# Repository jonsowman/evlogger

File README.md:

Electric Vehicle Datalogger
===========================

This project uses an MSP430 (specifically, the MSP430F5529) to log data from
various channels to be used on an electric vehicle. This project is designed
for use on the MSP-EXP430F5529LP experimentation board which is available from
Texas Instruments.  

Documentation at http://jonsowman.github.com/evlogger.  

Released into the public domain by Jon Sowman, 2014.  

[Get in touch](mailto:j.sowman@soton.ac.uk)

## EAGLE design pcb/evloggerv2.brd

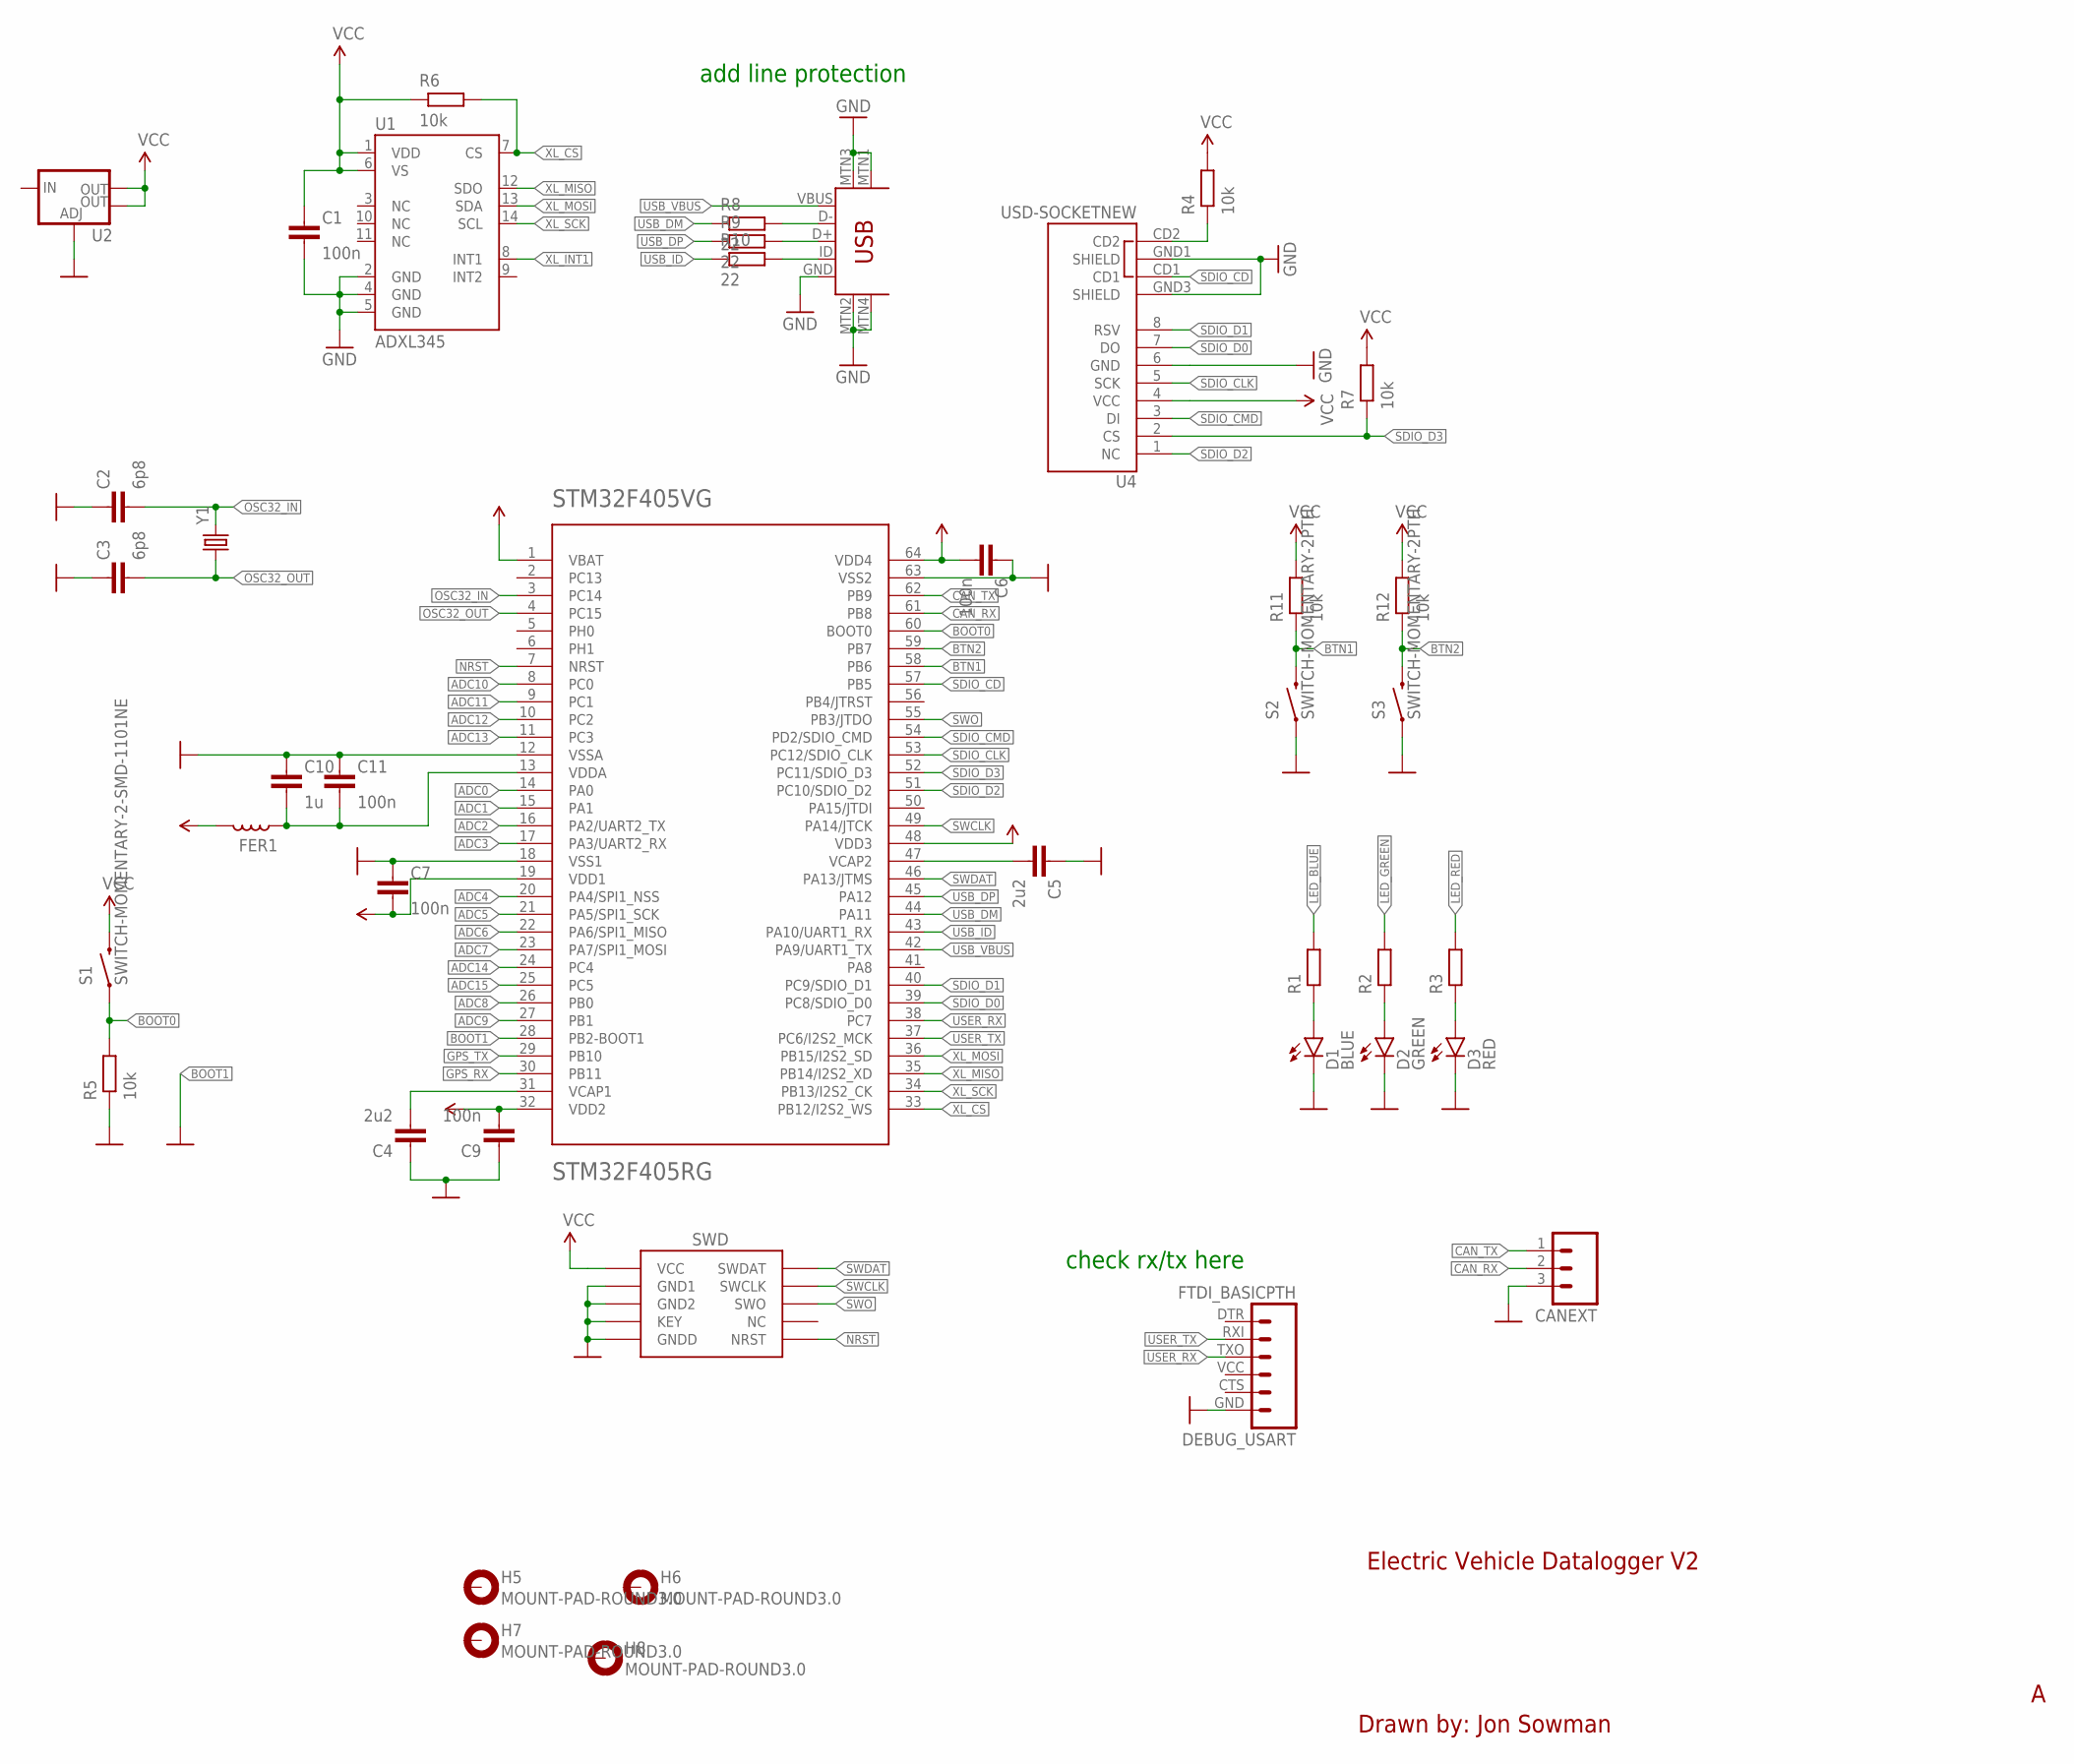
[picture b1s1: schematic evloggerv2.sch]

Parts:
C1, C6, C7, C9, C11: 100n; C0603-N
C2, C3: 6p8; C0603-N
C4, C5: 2u2; C0603-N
C10: 1u; C0603-N
CANEXT: M03PTH; 1X03
D1: BLUE; LED-0603
D2: GREEN; LED-0603
D3: RED; LED-0603
DEBUG_USART: FTDI_BASICPTH; FTDI_BASIC
FER1: INDUCTOR0603-N; L0603-N
H5, H6, H7, H8: MOUNT-PAD-ROUND3.0; 3,0-PAD
R1, R2, R3: RESISTOR0603-N; R0603-N
R4, R5, R6, R7, R11, R12: 10k; R0603-N
R8, R9, R10: 22; R0603-N
S1: SWITCH-MOMENTARY-2-SMD-1101NE; TACTILE-SWITCH-1101NE
S2, S3: SWITCH-MOMENTARY-2PTH; TACTILE-PTH
STM32F405VG: STM32F405RG; TQFP64
U1: ADXL345; LGA14
U2: V_REG_LM1117SOT223; SOT223
U4: USD-SOCKETNEW; MICRO-SD-SOCKET-PP
U$1: SWD_PTH_SHROUD
U$2: USB-MINIB-5PIN; USB-MINIB
Y1: CRYSTAL32-SMD; CRYSTAL-32KHZ-SMD

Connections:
ADC0: STM32F405VG.14 (PA0)
ADC1: STM32F405VG.15 (PA1)
ADC2: STM32F405VG.16 (PA2/UART2_TX)
ADC3: STM32F405VG.17 (PA3/UART2_RX)
ADC4: STM32F405VG.20 (PA4/SPI1_NSS)
ADC5: STM32F405VG.21 (PA5/SPI1_SCK)
ADC6: STM32F405VG.22 (PA6/SPI1_MISO)
ADC7: STM32F405VG.23 (PA7/SPI1_MOSI)
ADC8: STM32F405VG.26 (PB0)
ADC9: STM32F405VG.27 (PB1)
ADC10: STM32F405VG.8 (PC0)
ADC11: STM32F405VG.9 (PC1)
ADC12: STM32F405VG.10 (PC2)
ADC13: STM32F405VG.11 (PC3)
ADC14: STM32F405VG.24 (PC4)
ADC15: STM32F405VG.25 (PC5)
BOOT0: R5.2, S1.P$1 (1), STM32F405VG.60 (BOOT0)
BOOT1: STM32F405VG.28 (PB2-BOOT1)
BTN1: R11.1, S2.3 (2), STM32F405VG.58 (PB6)
BTN2: R12.1, S3.3 (2), STM32F405VG.59 (PB7)
CAN_RX: CANEXT.2, STM32F405VG.61 (PB8)
CAN_TX: CANEXT.1, STM32F405VG.62 (PB9)
GND: C1.2, C2.1, C3.1, C4.1, C5.1, C6.1, C7.1, C9.1, C10.1, C11.1, CANEXT.3, D1.C, D2.C, D3.C, DEBUG_USART.GND (6), R5.1, S2.1, S3.1, STM32F405VG.18 (VSS1), STM32F405VG.63 (VSS2), U1.2 (GND), U1.4 (GND), U1.5 (GND), U2.1 (ADJ), U4.6 (GND), U4.GND1 (SHIELD), U4.GND3 (SHIELD), U$1.3 (GND1), U$1.5 (GND2), U$1.7 (KEY), U$1.9 (GNDD), U$2.GND, U$2.MTN1 (MTN2), U$2.MTN2 (MTN3), U$2.MTN3 (MTN1), U$2.MTN4
GPS_RX: STM32F405VG.30 (PB11)
GPS_TX: STM32F405VG.29 (PB10)
LED_BLUE: R1.2
LED_GREEN: R2.2
LED_RED: R3.2
unnamed: R4.1, U4.CD2
unnamed: C4.2, STM32F405VG.31 (VCAP1)
unnamed: C5.2, STM32F405VG.47 (VCAP2)
unnamed: C10.2, C11.2, FER1.1, STM32F405VG.13 (VDDA)
unnamed: D3.A, R3.1
unnamed: D2.A, R2.1
unnamed: D1.A, R1.1
unnamed: R8.2, U$2.D-
unnamed: R9.2, U$2.D+
unnamed: R10.2, U$2.ID
NRST: STM32F405VG.7 (NRST), U$1.10 (NRST)
OSC32_IN: C2.2, STM32F405VG.3 (PC14), Y1.X2 (2)
OSC32_OUT: C3.2, STM32F405VG.4 (PC15), Y1.X1 (1)
SDIO_CD: STM32F405VG.57 (PB5), U4.CD1
SDIO_CLK: STM32F405VG.53 (PC12/SDIO_CLK), U4.5 (SCK)
SDIO_CMD: STM32F405VG.54 (PD2/SDIO_CMD), U4.3 (DI)
SDIO_D0: STM32F405VG.39 (PC8/SDIO_D0), U4.7 (DO)
SDIO_D1: STM32F405VG.40 (PC9/SDIO_D1), U4.8 (RSV)
SDIO_D2: STM32F405VG.51 (PC10/SDIO_D2), U4.1 (NC)
SDIO_D3: R7.1, STM32F405VG.52 (PC11/SDIO_D3), U4.2 (CS)
SWCLK: STM32F405VG.49 (PA14/JTCK), U$1.4 (SWCLK)
SWDAT: STM32F405VG.46 (PA13/JTMS), U$1.2 (SWDAT)
SWO: STM32F405VG.55 (PB3/JTDO), U$1.6 (SWO)
USB_DM: R8.1, STM32F405VG.44 (PA11)
USB_DP: R9.1, STM32F405VG.45 (PA12)
USB_ID: R10.1, STM32F405VG.43 (PA10/UART1_RX)
USB_VBUS: STM32F405VG.42 (PA9/UART1_TX), U$2.VBUS
USER_RX: DEBUG_USART.TXO (3), STM32F405VG.38 (PC7)
USER_TX: DEBUG_USART.RXI (2), STM32F405VG.37 (PC6/I2S2_MCK)
VCC: C1.1, C6.2, C7.2, C9.2, FER1.2, R4.2, R6.1, R7.2, R11.2, R12.2, S1.P$2 (2), STM32F405VG.1 (VBAT), STM32F405VG.19 (VDD1), STM32F405VG.32 (VDD2), STM32F405VG.48 (VDD3), STM32F405VG.64 (VDD4), U1.1 (VDD), U1.6 (VS), U2.2 (OUT), U2.4 (OUT), U4.4 (VCC), U$1.1 (VCC)
XL_CS: R6.2, STM32F405VG.33 (PB12/I2S2_WS), U1.7 (CS)
XL_INT1: U1.8 (INT1)
XL_MISO: STM32F405VG.35 (PB14/I2S2_XD), U1.12 (SDO)
XL_MOSI: STM32F405VG.36 (PB15/I2S2_SD), U1.13 (SDA)
XL_SCK: STM32F405VG.34 (PB13/I2S2_CK), U1.14 (SCL)

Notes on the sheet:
check rx/tx here
add line protection
Drawn by: Jon Sowman
Electric Vehicle Datalogger V2

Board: 2 copper layers, 42 parts (0 on the bottom side), 40 nets, no tracks yet.

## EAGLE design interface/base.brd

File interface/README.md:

# Interface between EVLogger and sensors/vehicle

Logger samples ADC channels:  

* 6  - P6.6
* 7  - P6.7
* 12 - P7.0
* 13 - P7.1
* 14 - P7.2
* 15 - P7.3
* 5  - User potentiometer

6 and 7 are pins 2 and 14 on Pin Header J4  
12, 13, 14, 15 are pins 2, 4, 6, 8 on Pin Header J5  

For GPS, UCA1 is available on Pin Header J4, but this is shared with the ez430
programmer and requires removing/adding jumpers.  

* 1 - VCC
* 3 - RXD
* 5 - TXD
* 13 - GND

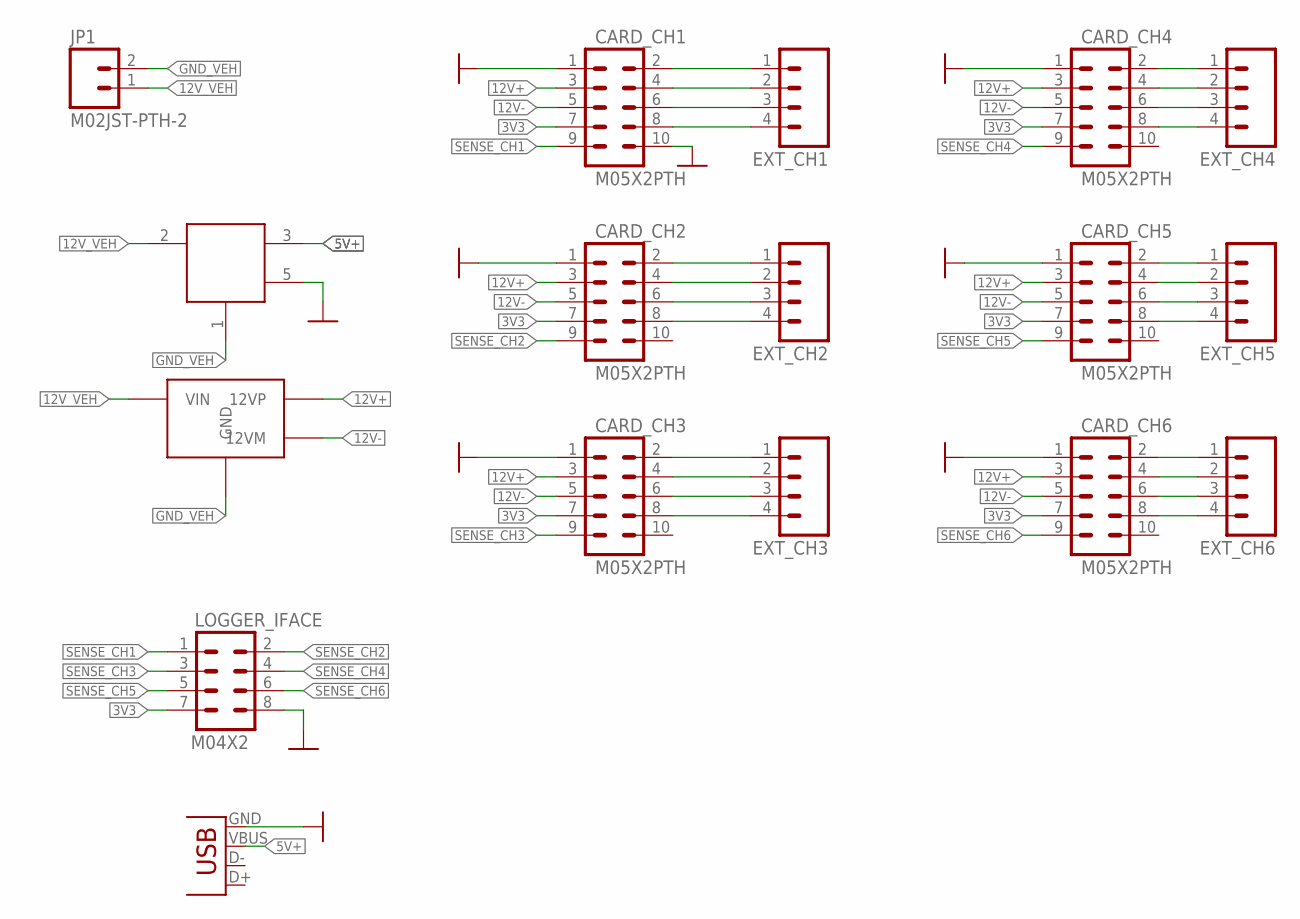
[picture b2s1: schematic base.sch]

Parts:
CARD_CH1, CARD_CH2, CARD_CH3, CARD_CH4, CARD_CH5, CARD_CH6: M05X2PTH; AVR_ICSP
EXT_CH1, EXT_CH2, EXT_CH3, EXT_CH4, EXT_CH5, EXT_CH6: M04PTH; 1X04
JP1: M02JST-PTH-2; JST-2-PTH
JP2: USB-A-S
LOGGER_IFACE: M04X2; 2X4
U$1: NMXS1205UC_PTH
U$2: TMR3122_12_CONV_PTH

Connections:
3V3: CARD_CH1.7, CARD_CH2.7, CARD_CH3.7, CARD_CH4.7, CARD_CH5.7, CARD_CH6.7, LOGGER_IFACE.7
5V+: JP2.VBUS, U$1.3 (5VOUT)
12V+: CARD_CH1.3, CARD_CH2.3, CARD_CH3.3, CARD_CH4.3, CARD_CH5.3, CARD_CH6.3, U$2.5 (12VP)
12V-: CARD_CH1.5, CARD_CH2.5, CARD_CH3.5, CARD_CH4.5, CARD_CH5.5, CARD_CH6.5, U$2.6 (12VM)
12V_VEH: JP1.1, U$1.2 (VIN), U$2.2 (VIN)
GND: CARD_CH1.1, CARD_CH1.10, CARD_CH2.1, CARD_CH3.1, CARD_CH4.1, CARD_CH5.1, CARD_CH6.1, JP2.GND, LOGGER_IFACE.8, U$1.5 (GNDOUT)
GND_VEH: JP1.2, U$1.1 (GND), U$2.1 (GND)
unnamed: CARD_CH1.2, EXT_CH1.1
unnamed: CARD_CH1.4, EXT_CH1.2
unnamed: CARD_CH1.6, EXT_CH1.3
unnamed: CARD_CH1.8, EXT_CH1.4
unnamed: CARD_CH2.2, EXT_CH2.1
unnamed: CARD_CH2.4, EXT_CH2.2
unnamed: CARD_CH2.6, EXT_CH2.3
unnamed: CARD_CH2.8, EXT_CH2.4
unnamed: CARD_CH3.2, EXT_CH3.1
unnamed: CARD_CH3.4, EXT_CH3.2
unnamed: CARD_CH3.6, EXT_CH3.3
unnamed: CARD_CH3.8, EXT_CH3.4
unnamed: CARD_CH4.2, EXT_CH4.1
unnamed: CARD_CH4.4, EXT_CH4.2
unnamed: CARD_CH4.6, EXT_CH4.3
unnamed: CARD_CH4.8, EXT_CH4.4
unnamed: CARD_CH5.2, EXT_CH5.1
unnamed: CARD_CH5.4, EXT_CH5.2
unnamed: CARD_CH5.6, EXT_CH5.3
unnamed: CARD_CH5.8, EXT_CH5.4
unnamed: CARD_CH6.2, EXT_CH6.1
unnamed: CARD_CH6.4, EXT_CH6.2
unnamed: CARD_CH6.6, EXT_CH6.3
unnamed: CARD_CH6.8, EXT_CH6.4
SENSE_CH1: CARD_CH1.9, LOGGER_IFACE.1
SENSE_CH2: CARD_CH2.9, LOGGER_IFACE.2
SENSE_CH3: CARD_CH3.9, LOGGER_IFACE.3
SENSE_CH4: CARD_CH4.9, LOGGER_IFACE.4
SENSE_CH5: CARD_CH5.9, LOGGER_IFACE.5
SENSE_CH6: CARD_CH6.9, LOGGER_IFACE.6

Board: 2 copper layers, 17 parts (0 on the bottom side), 37 nets, no tracks yet.

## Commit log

2013-10-26 Initial commit with working XT2 referenced FLL clocking
2013-10-26 Adjusted for 20MHz operation
2013-10-26 Removed oscillator checking for now since I no longer care
2013-10-26 First attempt at getting the UART working. It doesn't work. It's late and I'm going to sleep.
2013-10-27 UART working but timing is a bit out, need to check oscillator
2013-11-12 UART working at 9600 baud, turns out ez430 programmer can't support higher than this.
2013-11-12 Added uart_debug to make my life a bit easier
2013-11-13 Started work on ADC but not quite working yet
2013-11-16 Moved delay function into a module so can be used elsewhere
2013-11-16 Ignore vim's swap files
2013-11-16 ADC working - I'm an idiot. See commit for details :(
2013-11-16 Forgot to make _uart_tx() static
2013-11-16 Timer0 set up for 1ms, system ticks counter created
2013-11-16 Function pointers!
2013-11-16 Added registration of 10ms and 100ms functions to the clock module (just one of each at the moment)
2013-11-17 Added _BV() macro to typedefs, sd_init() created for setting up UCSI for SPI for SD card
2013-11-17 Added fatfs - not building yet due to DIR being #defined in msp430x header. Sigh
2013-11-17 Fixed the #define DIR thing, and a function definition mismatch. Not building due to get_fattime() not defined
2013-11-17 Fixed build issue, builds and runs, fatfs not tested yet. get_fattime() returns 0 (invalid) at the moment. Fix this please
2014-01-24 Fixed SD card issue, SPI clock pol was wrong. Sigh
2014-01-24 Delay before trying to mount the card so that the SD timer functionality can sort itself out
2014-01-25 Put fast SPI back to 200kHz
2014-02-02 Included HAL bits for LCD from TI example code, with a couple of small modifications
2014-02-02 Hello worl on the lcd. Holy grail achieved
2014-02-02 Commented SPI init stuff from the LCD driver, since it's already done in the SD card init
2014-02-02 Displaying fatfs stuff on lcd
2014-02-02 Clear the line on the LCD before writing new text
2014-02-02 Disabled LCD for a minute to test why fatfs can't write to the card
2014-02-02 Reading from file on SD card working
2014-02-02 Fixed SD card problems, buffer overflow. Made sure that doesn't happen again
2014-02-03 OK ff does actually handle string term properly
2014-02-03 Display SD usage on lcd
2014-02-03 Added accelerometer and display on lcd
2014-02-03 Oops, forgot to remove a delay
2014-02-03 Reorganising things
2014-02-03 Moved logging function to its own file, starting work on logging
2014-02-03 Button S1 working via interrupts
2014-02-03 Button S1 now controlling logging, TA1 setup up as logging timer
2014-02-03 Moved fatfs stuff over to the logging module
2014-02-03 Show logging status on the lcd
2014-02-03 Added sd_setup() prototype to logger.h header
2014-02-04 Fixed string length counting when writing to file
2014-02-04 Moved sd_init() to logger_init()
2014-02-04 Opening and closing log file on button press
2014-02-05 Remove LCD stuff temporarily
2014-02-05 Included TI version of fatfs, appears to work properly - f_sync returns zero
2014-02-05 Added SD HAL layer and mmc functionality from ti example code
2014-02-05 Removed F_CPU repeated defines before this bites me
2014-02-05 Removed custom SD init function since the TI lib already does it.
2014-02-05 Don't need to call SDCard_init() explicitly
2014-02-05 Moved SD stuff to logger module
2014-02-05 Removed needless wait
2014-02-05 Moved LCD update functionality to logger subsystem
2014-02-05 Showing SD card usage on LCD screen, updated 1/second
2014-02-05 Turned the brightness down so I'm not blinded
2014-02-06 Don't call getfree before fatfs struct has data in it
2014-02-06 Testing writing a whole sector (512 bytes)
2014-02-06 Detect and warn if no SD card inserted
2014-02-06 Swapped heartbeat and SD write LEDs round
2014-02-06 Button S1 starts and stops TA1 and writes logging on/off to lcd
2014-02-06 Started work on the ring buffer for SD transactions
2014-02-06 Working ring buffer read() and getfree()
2014-02-06 Working getused() and made length and mask a property of the buffer rather than defines
2014-02-06 Checking we don't overwrite/overread the buffer
2014-02-06 Working logging!!!!!!
2014-02-06 Logging at 1kHz, forgot a _delay() oops
2014-02-06 Debounce the switches and go back to 1024 byte SD write buffer
2014-02-06 Remove heartbeat LED so I can see SD_BUSY led
2014-02-06 Update lcd from main logger loop, too slow for interrupts. Monitor for buffer overflow
2014-02-06 Expanded the buffer to accommodate writing 6 channels
2014-02-06 Slowed down LCD updates otherwise it's unreadable
2014-02-06 A couple of cheeky macros should make the main logger loop run a bit quicker
2014-02-06 Removed normal getfree and getused for ringbuf since why would I ever use them?
2014-02-07 When stopping logging, write anything left in the SD buffer to the card
2014-02-07 a spurious line break
2014-02-10 Removed function called from system clock interface since no longer used
2014-02-10 Moved init of system clock to system clock module
2014-02-10 Removed redundant clock def prototypes. Updated copyright notice
2014-02-10 Moved _delay_ms() to system
2014-02-10 Removed delay.{h,c} since no longer required
2014-02-10 Removed includes for delay.h, now builds again
2014-02-10 Switched to 25MHz core clock, using HAL layer for PMM from Ti
2014-02-10 Fixed the system clock to count 1ms properly at 25MHz core clock
2014-02-10 Fixed defines in system
2014-02-11 Restructured the source directory a bit
2014-02-11 Use a seperate build dir to avoid clutter
2014-02-11 I think I have a working makefile?
2014-02-11 Oops, dependencies in Makefile were broken due to build/. Now fixed.
2014-02-12 Only generate local .h dependencies, not system ones
2014-02-12 ADC running in sequential conversion mode, need to set up DMA now
2014-02-12 DMA working for transferring ADC readings to a sample buffer
2014-02-13 Samplebuffer work started, not quite working yet
2014-02-14 Writing binary data to the log file
2014-02-14 Changed SampleBuffer to use all 16 bit values so that struct packing doesn't make my life hell
2014-02-25 typo
2014-03-02 testing accel, takes 30us per axis
2014-03-02 accel implementation working, not results tested yet
2014-03-02 this does work but is a bit dodgy. needs some rearchitecturing
2014-03-02 DMA accel working, not integrated yet, still in independent test mode
2014-03-02 command buffer stopped from going out of scope and being free()'d
2014-03-02 using DMAIFG flag to wait for end of conversion
2014-03-02 just some tidying, about to attempt putting accel data into sample buffer
2014-03-02 correctly sampling accel to the sample buffer using dma interrupt
2014-03-02 removed an unnecessary wait for tx buffer to be ready
2014-03-02 Moved CS deassert into the ISR
2014-03-02 used a define'd value from the library for the DMA IV source
2014-03-02 Better naming, removed some unused stuff from timer accel implementation
2014-03-02 More tidying
2014-03-02 DMA src and dest in setup since they don't change
2014-03-02 removed a redundant s
2014-03-02 DMA IFG is auto cleared by execution of the ISR
2014-03-03 Should be working DMA accel but isn't - attempt FSM based approach
2014-03-03 working on doc
2014-03-03 logger module docs completely
2014-03-03 more docs work
2014-03-03 updated docs, layout is nicer, added main page
2014-03-03 docs for the structs in the logger module
2014-03-03 ignore the docs build dir from git
2014-03-03 don't use dots in i.e. !!
2014-03-03 upgraded doxyfile and fixed warnings
2014-03-03 more docs
2014-03-03 Working FSM accel
2014-03-03 everything is STATIC
2014-03-03 removed all debug output
2014-03-03 removed led testing
2014-03-03 Log the accel as fast as possible, document static vars
2014-03-03 Removed accel offset stuff
2014-03-03 Tidied up docs even more, looking pretty complete now
2014-03-03 docs: dont extract all
2014-03-03 forgot to author/copyright update typedefs.h
2014-03-03 Fixed docs in accel files
2014-03-04 gross but working first run at the log file parser
2014-03-04 added header
2014-03-04 more docs again
2014-03-04 fixed typo in docs
2014-03-04 print in base 10
2014-06-26 Added interfacing and signal conditioning circuits
2014-06-26 Added transient voltage suppression diodes to op amp output
2014-10-07 Updated email addresses
2014-11-05 docs
2014-11-05 pushing doxygen'd docs
2014-11-05 Readme info
2014-11-10 Adding interface hardware
2015-08-25 added pinout
2015-08-25 formatting
2015-08-27 work on v2 pcb

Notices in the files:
parts and their libraries:
SparkFun-Connectors: Licensing: Creative Commons ShareAlike 4.0 International - https://creativecommons.org/licenses/by-sa/4.0
